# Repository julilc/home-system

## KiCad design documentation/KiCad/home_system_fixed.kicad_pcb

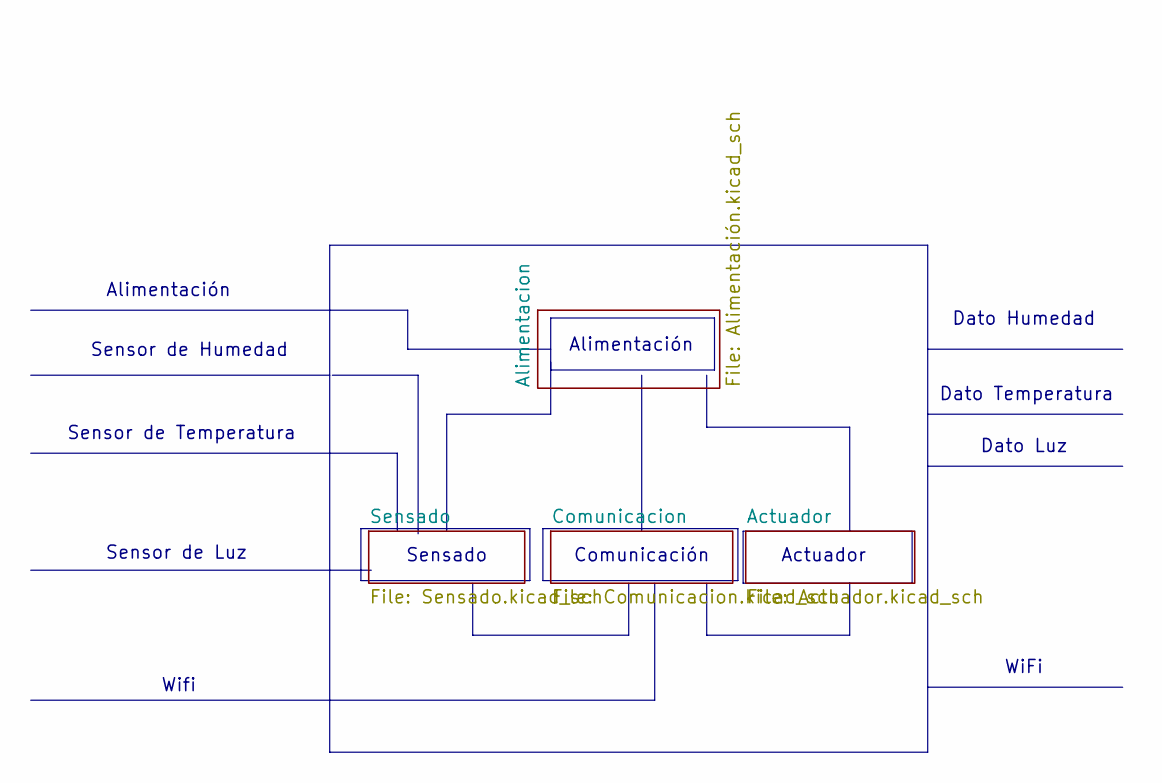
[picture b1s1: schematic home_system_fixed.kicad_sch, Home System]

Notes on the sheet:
Sensor de Humedad
Wifi
Dato Temperatura
Alimentación
Sensor de Temperatura
Dato Luz
Sensado
Dato Humedad
WiFi
Comunicación
Actuador
Sensor de Luz

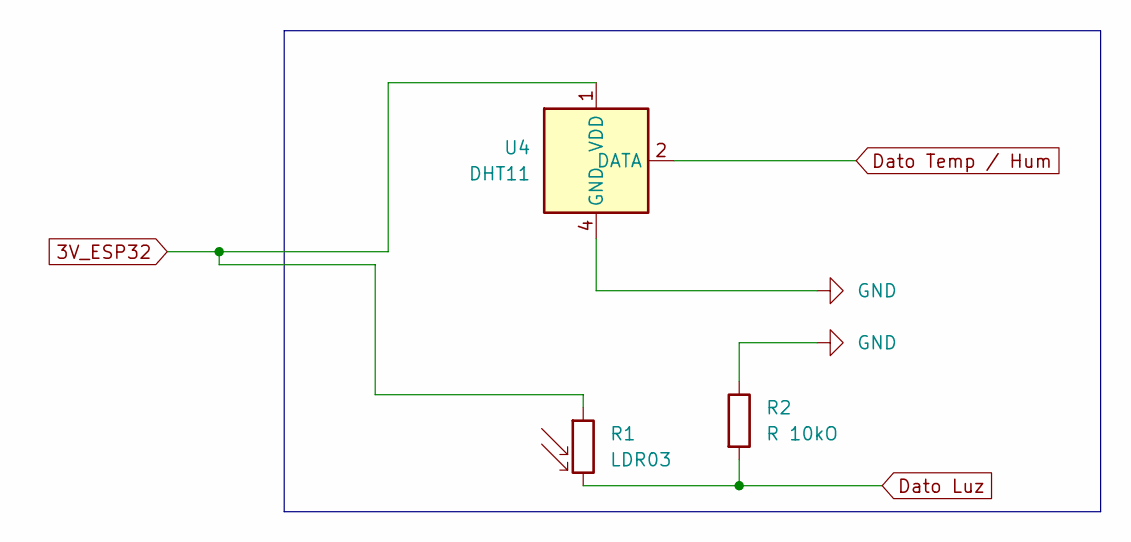
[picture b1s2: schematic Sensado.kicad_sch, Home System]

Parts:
R1: LDR03; R_LDR_10x8.5mm_P7.6mm_Vertical
R2: R 10kO; R_Axial_DIN0207_L6.3mm_D2.5mm_P10.16mm_Horizontal
U4: DHT11; Aosong_DHT11_5.5x12.0_P2.54mm

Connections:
3V_ESP32: R1.1, U4.1 (VDD); also elsewhere on the board
Dato Luz: R1.2, R2.2; also elsewhere on the board
Dato Temp / Hum: U4.2 (DATA); also elsewhere on the board
GND: R2.1, U4.4 (GND); also elsewhere on the board

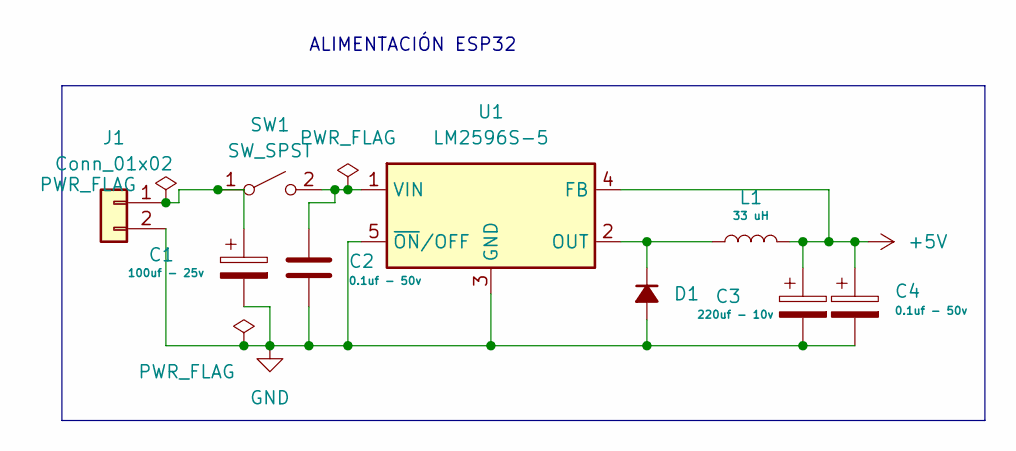
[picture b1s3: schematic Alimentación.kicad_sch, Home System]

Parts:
C1: 100uf - 25v; CP_Radial_D6.3mm_P2.50mm
C2, C4: 0.1uf - 50v; C_Disc_D5.0mm_W2.5mm_P5.00mm
C3: 220uf - 10v; CP_Radial_D6.3mm_P2.50mm
D1: D_DO-35_SOD27_P7.62mm_Horizontal
J1: Conn_01x02; TerminalBlock_Phoenix_MKDS-1,5-2-5.08_1x02_P5.08mm_Horizont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
L1: 33 uH; L_Radial_D10.0mm_P5.00mm_Fastron_07M
SW1: SW_SPST; SW_PUSH_6mm
U1: LM2596S-5; TO-263-5_TabPin3

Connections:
+5V: C3.1, C4.1, L1.2, U1.4 (FB); also elsewhere on the board
GND: C1.2, C2.2, C3.2, C4.2, D1.2 (A), J1.2, U1.3 (GND), U1.5 (~ON/OFF); also elsewhere on the board
unnamed: D1.1 (K), L1.1, U1.2 (OUT)
unnamed: C1.1, J1.1, SW1.1 (A)
unnamed: C2.1, SW1.2 (B), U1.1 (VIN)

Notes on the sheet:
ALIMENTACIÓN ESP32

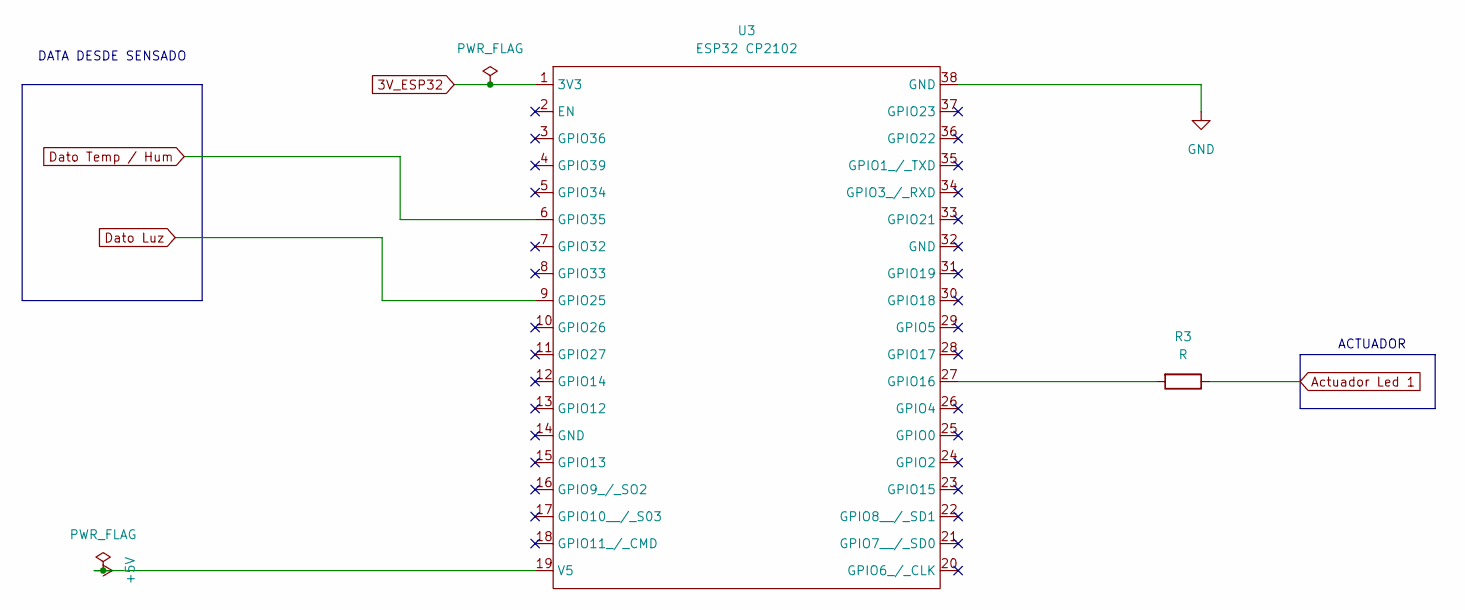
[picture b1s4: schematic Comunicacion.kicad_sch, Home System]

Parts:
R3: R; R_Axial_DIN0207_L6.3mm_D2.5mm_P10.16mm_Horizontal
U3: ESP32 CP2102; ESP32_38Pin

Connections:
3V_ESP32: U3.1 (3V3); also elsewhere on the board
+5V: U3.19 (V5); also elsewhere on the board
Actuador Led 1: R3.1; also elsewhere on the board
Dato Luz: U3.9 (GPIO25); also elsewhere on the board
Dato Temp / Hum: U3.6 (GPIO35); also elsewhere on the board
GND: U3.38 (GND); also elsewhere on the board
unnamed: R3.2, U3.27 (GPIO16)

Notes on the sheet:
ACTUADOR
DATA DESDE SENSADO

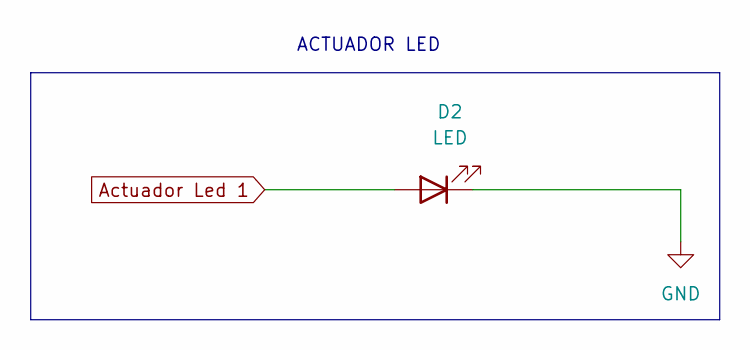
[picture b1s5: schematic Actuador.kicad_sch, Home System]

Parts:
D2: LED; LED_D5.0mm

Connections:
Actuador Led 1: D2.2 (A); also elsewhere on the board
GND: D2.1 (K); also elsewhere on the board

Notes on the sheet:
ACTUADOR LED

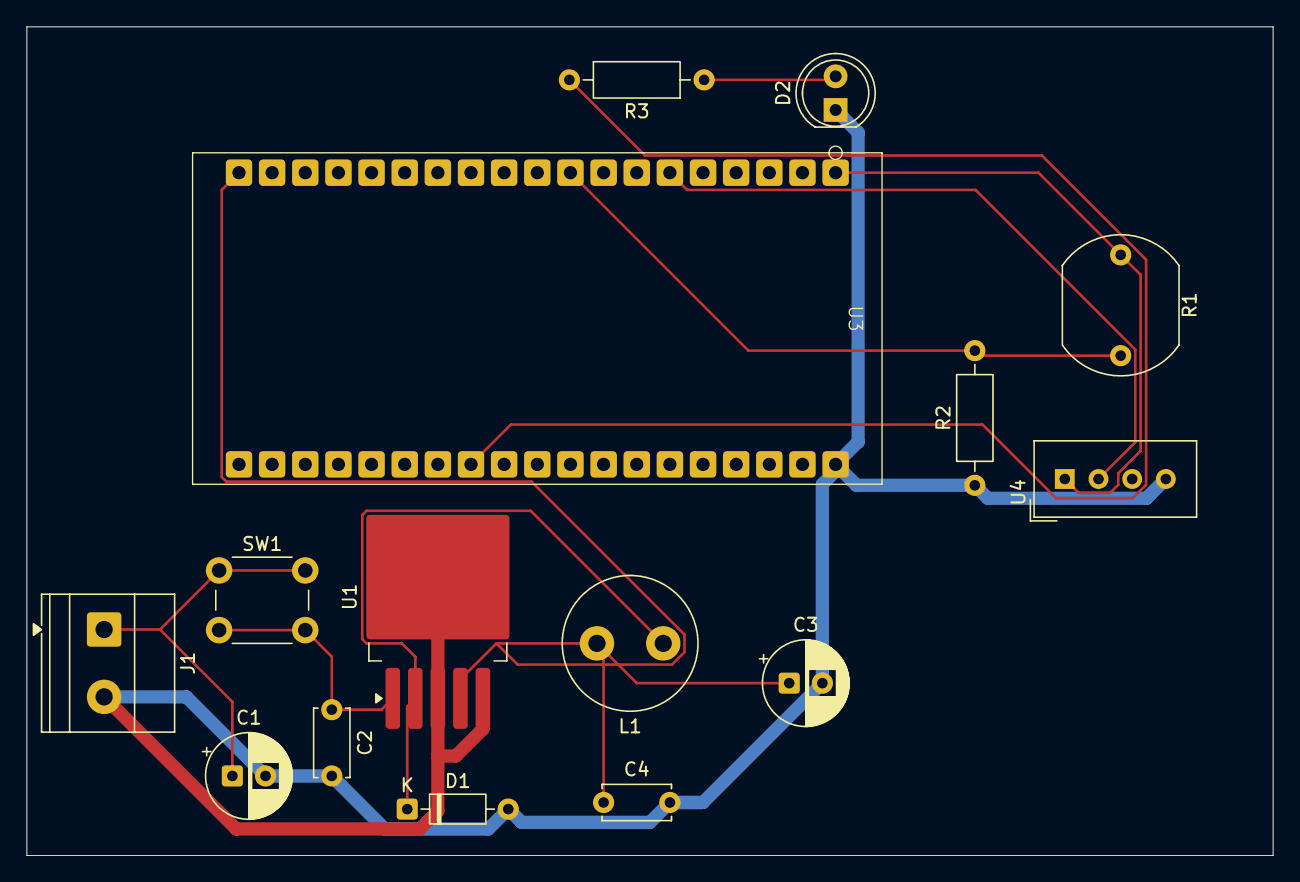
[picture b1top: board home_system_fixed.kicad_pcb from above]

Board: 2 copper layers, 94.0 x 62.5 mm, 15 parts (0 on the bottom side), 10 nets.
